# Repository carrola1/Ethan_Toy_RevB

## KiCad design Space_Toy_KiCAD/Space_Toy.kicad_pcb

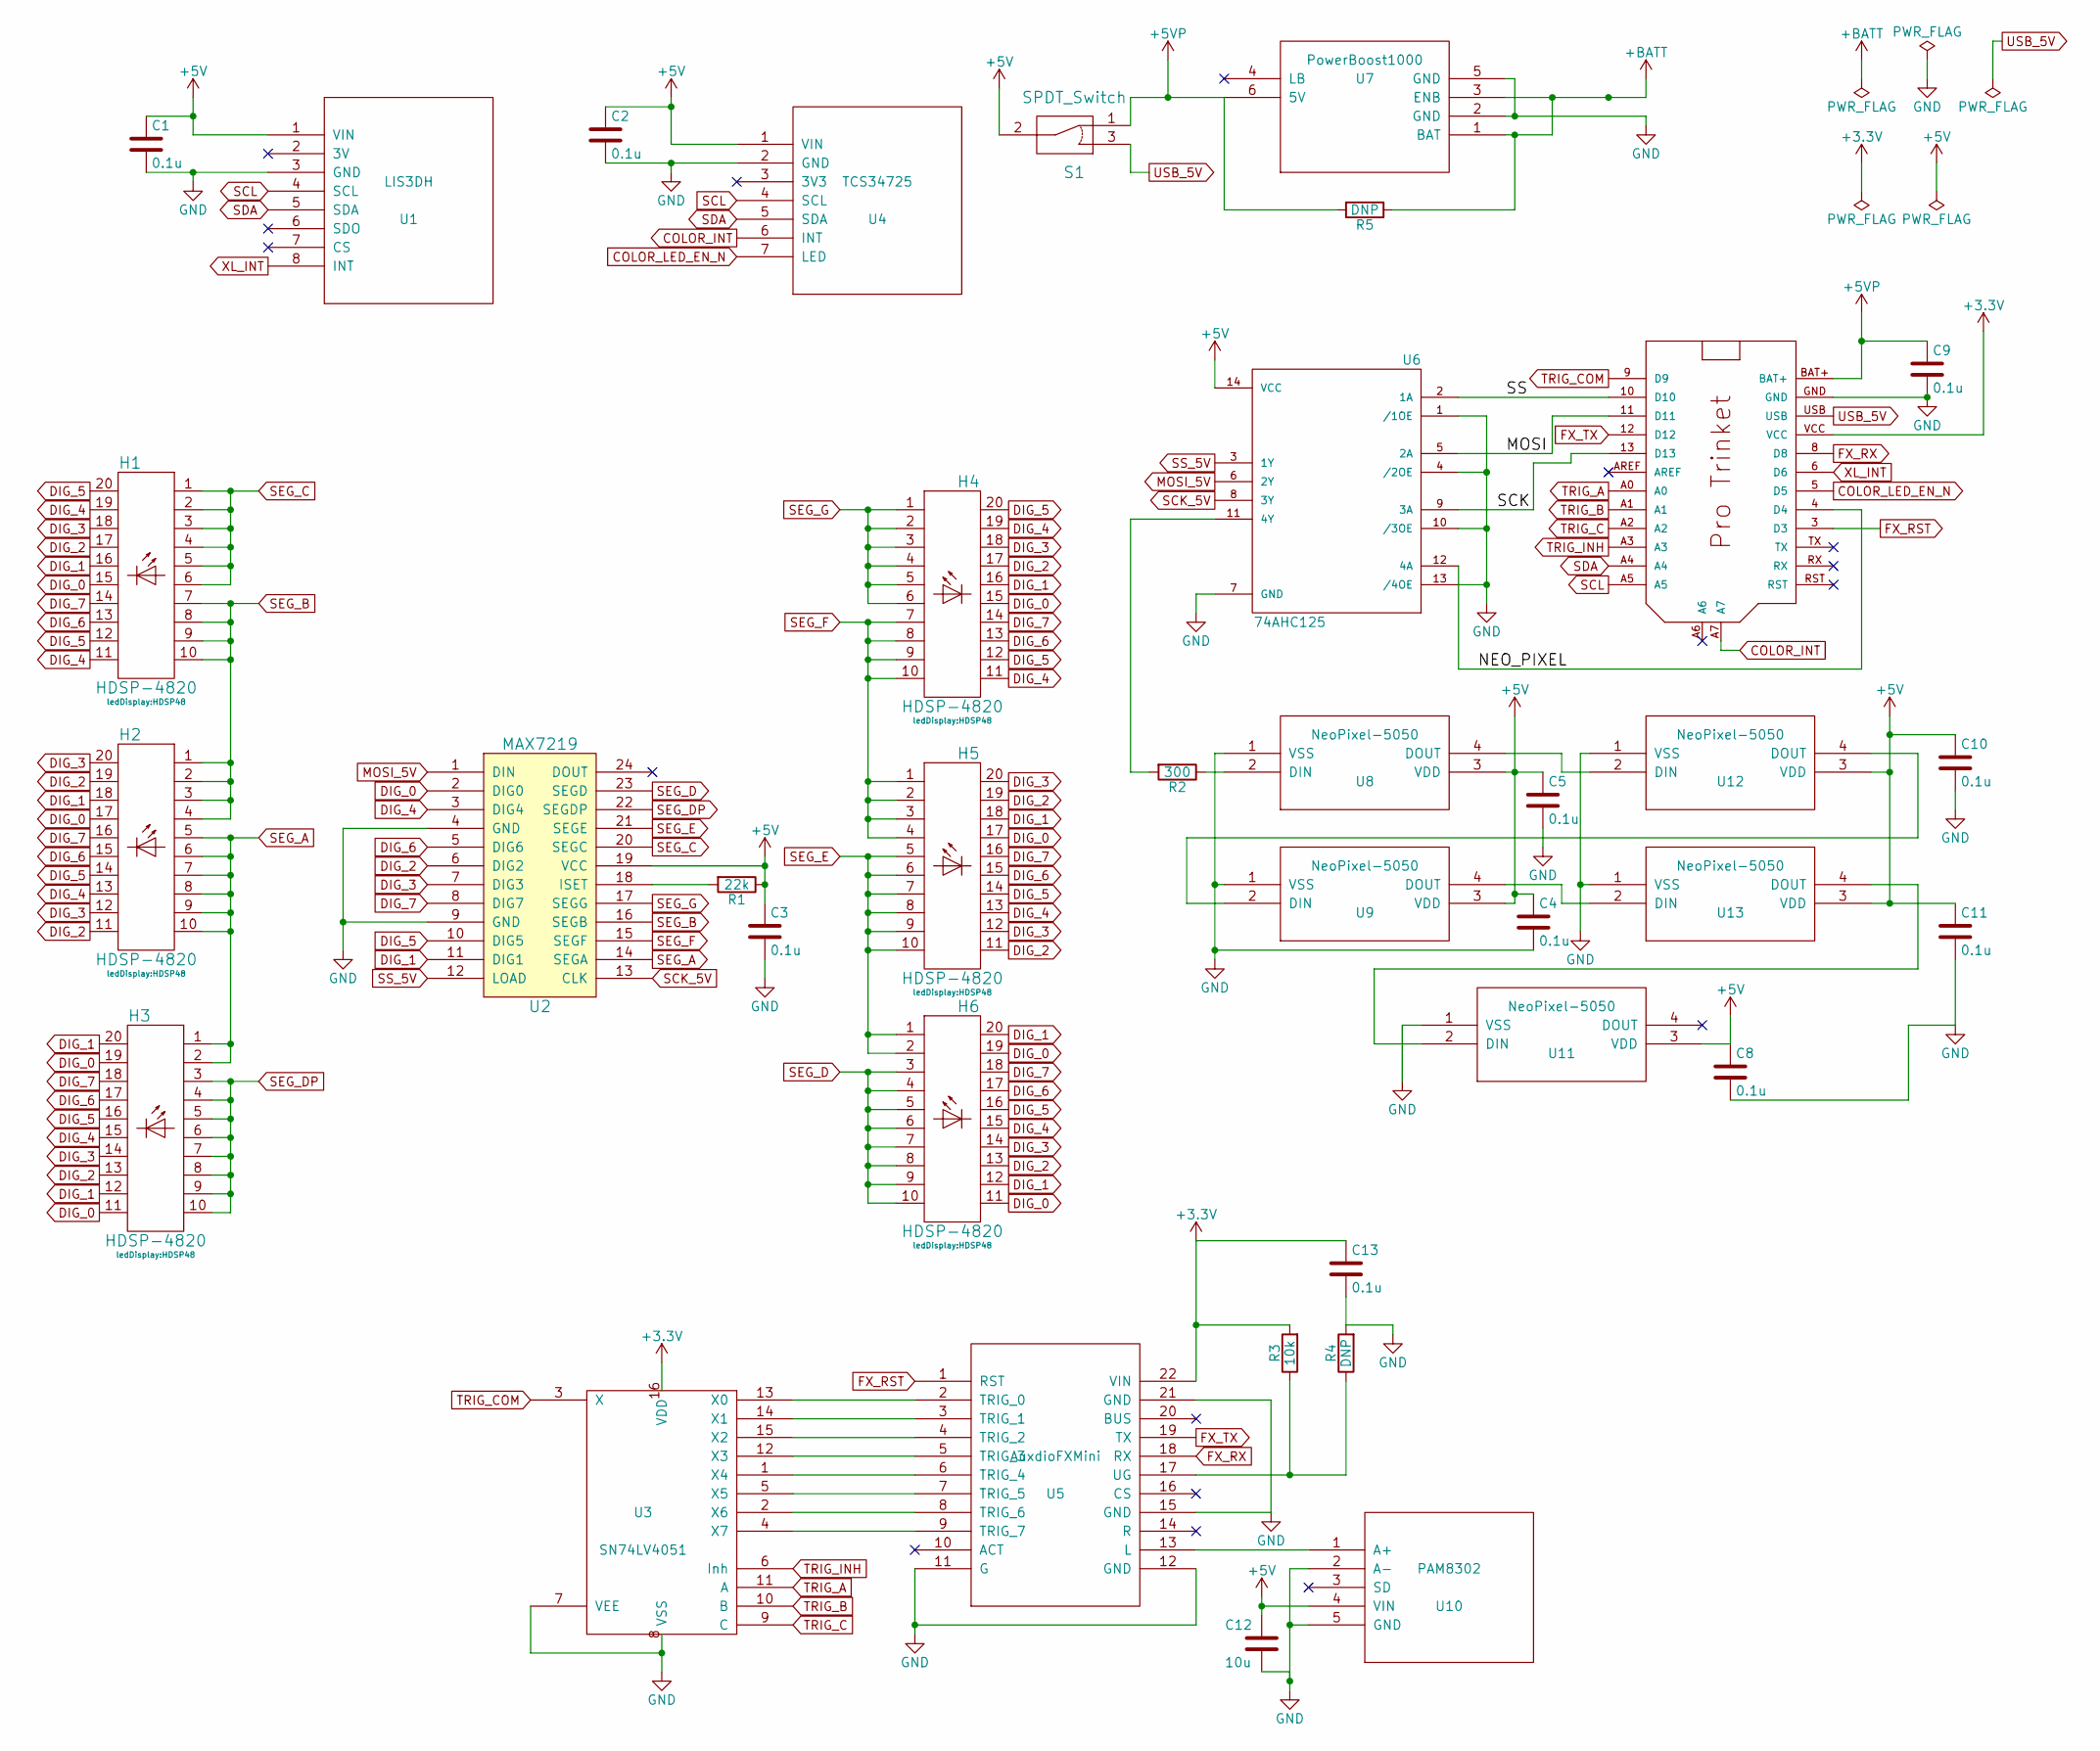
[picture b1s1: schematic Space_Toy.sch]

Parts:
C1, C2, C3, C4, C5, C8, C9, C10, C11, C13: 0.1u; C_0603_HandSoldering
C12: 10u; C_0603_HandSoldering
H1, H2, H3, H4, H5, H6: HDSP-4820; HDSP48
M1: PRO_TRINKET; PROTRINKET
R1: 22k; R_0805_HandSoldering
R2: 300; R_0805_HandSoldering
R3: 10k; R_0805_HandSoldering
R4, R5: DNP; R_0805_HandSoldering
S1: SPDT_Switch; SPDT
U1: LIS3DH
U2: MAX7219; DIP-24_W7.62mm_LongPads
U3: SN74LV4051; DIP-16_W7.62mm_LongPads
U4: TCS34725
U5: AuxdioFXMini; AudioFXMini
U6: 74AHC125; DIP-14_W7.62mm_LongPads
U7: PowerBoost1000
U8, U9, U11, U12, U13: NeoPixel-5050; NeoPixel5050
U10: PAM8302

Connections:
+3V3: C13.1, M1.VCC, R3.2, U3.16 (VDD), U5.22 (VIN)
+5V: C1.1, C2.1, C3.1, C4.1, C5.1, C8.1, C10.1, C11.1, C12.1, R1.1, S1.2, U1.1 (VIN), U2.19 (VCC), U4.1 (VIN), U6.14 (VCC), U8.3 (VDD), U9.3 (VDD), U10.4 (VIN), U11.3 (VDD), U12.3 (VDD), U13.3 (VDD)
+5VP: C9.1, M1.BAT+, R5.2, S1.1, U7.6 (5V)
+BATT: R5.1, U7.1 (BAT), U7.3 (ENB)
/MOSI: M1.11 (D11), U6.5 (2A)
/NEO_PIXEL: M1.4 (D4), U6.12 (4A)
/SCK: M1.13 (D13), U6.9 (3A)
/SS: M1.10 (D10), U6.2 (1A)
COLOR_INT: M1.A7, U4.6 (INT)
COLOR_LED_EN_N: M1.5 (D5), U4.7 (LED)
DIG_0: H1.15 (K), H2.17 (K), H3.11 (K), H3.19 (K), H4.15 (K), H5.17 (K), H6.11 (K), H6.19 (K), U2.2 (DIG0)
DIG_1: H1.16 (K), H2.18 (K), H3.12 (K), H3.20 (K), H4.16 (K), H5.18 (K), H6.12 (K), H6.20 (K), U2.11 (DIG1)
DIG_2: H1.17 (K), H2.11 (K), H2.19 (K), H3.13 (K), H4.17 (K), H5.11 (K), H5.19 (K), H6.13 (K), U2.6 (DIG2)
DIG_3: H1.18 (K), H2.12 (K), H2.20 (K), H3.14 (K), H4.18 (K), H5.12 (K), H5.20 (K), H6.14 (K), U2.7 (DIG3)
DIG_4: H1.11 (K), H1.19 (K), H2.13 (K), H3.15 (K), H4.11 (K), H4.19 (K), H5.13 (K), H6.15 (K), U2.3 (DIG4)
DIG_5: H1.12 (K), H1.20 (K), H2.14 (K), H3.16 (K), H4.12 (K), H4.20 (K), H5.14 (K), H6.16 (K), U2.10 (DIG5)
DIG_6: H1.13 (K), H2.15 (K), H3.17 (K), H4.13 (K), H5.15 (K), H6.17 (K), U2.5 (DIG6)
DIG_7: H1.14 (K), H2.16 (K), H3.18 (K), H4.14 (K), H5.16 (K), H6.18 (K), U2.8 (DIG7)
FX_RST: M1.3 (D3), U5.1 (RST)
FX_RX: M1.8 (D8), U5.18 (RX)
FX_TX: M1.12 (D12), U5.19 (TX)
GND: C1.2, C2.2, C3.2, C4.2, C5.2, C8.2, C9.2, C10.2, C11.2, C12.2, C13.2, M1.GND, R4.2, U1.3 (GND), U2.4 (GND), U2.9 (GND), U3.7 (VEE), U3.8 (VSS), U4.2 (GND), U5.11 (G), U5.12 (GND), U5.15 (GND), U5.21 (GND), U6.1 (/1OE), U6.4 (/2OE), U6.7 (GND), U6.10 (/3OE), U6.13 (/4OE), U7.2 (GND), U7.5 (GND), U8.1 (VSS), U9.1 (VSS), U10.2 (A-), U10.5 (GND), U11.1 (VSS), U12.1 (VSS), U13.1 (VSS)
MOSI_5V: U2.1 (DIN), U6.6 (2Y)
unnamed: R1.2, U2.18 (ISET)
unnamed: R2.1, U8.2 (DIN)
unnamed: R2.2, U6.11 (4Y)
unnamed: R3.1, R4.1, U5.17 (UG)
unnamed: U3.1 (X4), U5.6 (TRIG_4)
unnamed: U3.2 (X6), U5.8 (TRIG_6)
unnamed: U3.4 (X7), U5.9 (TRIG_7)
unnamed: U3.5 (X5), U5.7 (TRIG_5)
unnamed: U3.12 (X3), U5.5 (TRIG_3)
unnamed: U3.13 (X0), U5.2 (TRIG_0)
unnamed: U3.14 (X1), U5.3 (TRIG_1)
unnamed: U3.15 (X2), U5.4 (TRIG_2)
unnamed: U5.13 (L), U10.1 (A+)
unnamed: U11.2 (DIN), U13.4 (DOUT)
unnamed: U8.4 (DOUT), U12.2 (DIN)
unnamed: U9.2 (DIN), U12.4 (DOUT)
unnamed: U9.4 (DOUT), U13.2 (DIN)
SCK_5V: U2.13 (CLK), U6.8 (3Y)
SCL: M1.A5, U1.4 (SCL), U4.4 (SCL)
SDA: M1.A4, U1.5 (SDA), U4.5 (SDA)
SEG_A: H2.5 (A), H2.6 (A), H2.7 (A), H2.8 (A), H2.9 (A), H2.10 (A), H3.1 (A), H3.2 (A), U2.14 (SEGA)
SEG_B: H1.7 (A), H1.8 (A), H1.9 (A), H1.10 (A), H2.1 (A), H2.2 (A), H2.3 (A), H2.4 (A), U2.16 (SEGB)
SEG_C: H1.1 (A), H1.2 (A), H1.3 (A), H1.4 (A), H1.5 (A), H1.6 (A), U2.20 (SEGC)
SEG_D: H6.3 (A), H6.4 (A), H6.5 (A), H6.6 (A), H6.7 (A), H6.8 (A), H6.9 (A), H6.10 (A), U2.23 (SEGD)
SEG_DP: H3.3 (A), H3.4 (A), H3.5 (A), H3.6 (A), H3.7 (A), H3.8 (A), H3.9 (A), H3.10 (A), U2.22 (SEGDP)
SEG_E: H5.5 (A), H5.6 (A), H5.7 (A), H5.8 (A), H5.9 (A), H5.10 (A), H6.1 (A), H6.2 (A), U2.21 (SEGE)
SEG_F: H4.7 (A), H4.8 (A), H4.9 (A), H4.10 (A), H5.1 (A), H5.2 (A), H5.3 (A), H5.4 (A), U2.15 (SEGF)
SEG_G: H4.1 (A), H4.2 (A), H4.3 (A), H4.4 (A), H4.5 (A), H4.6 (A), U2.17 (SEGG)
SS_5V: U2.12 (LOAD), U6.3 (1Y)
TRIG_A: M1.A0, U3.11 (A)
TRIG_B: M1.A1, U3.10 (B)
TRIG_C: M1.A2, U3.9 (C)
TRIG_COM: M1.9 (D9), U3.3 (X)
TRIG_INH: M1.A3, U3.6 (Inh)
USB_5V: M1.USB, S1.3
XL_INT: M1.6 (D6), U1.8 (INT)

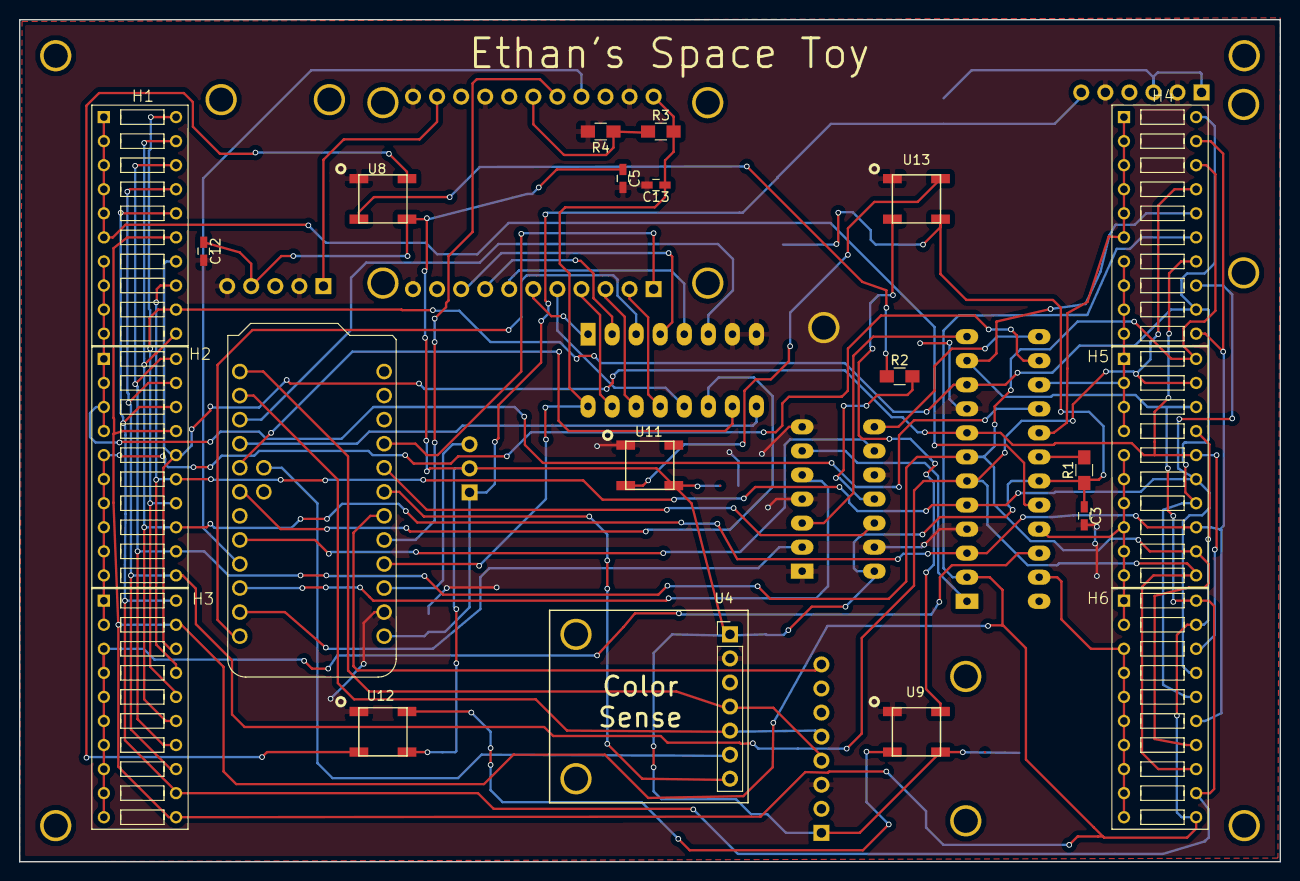
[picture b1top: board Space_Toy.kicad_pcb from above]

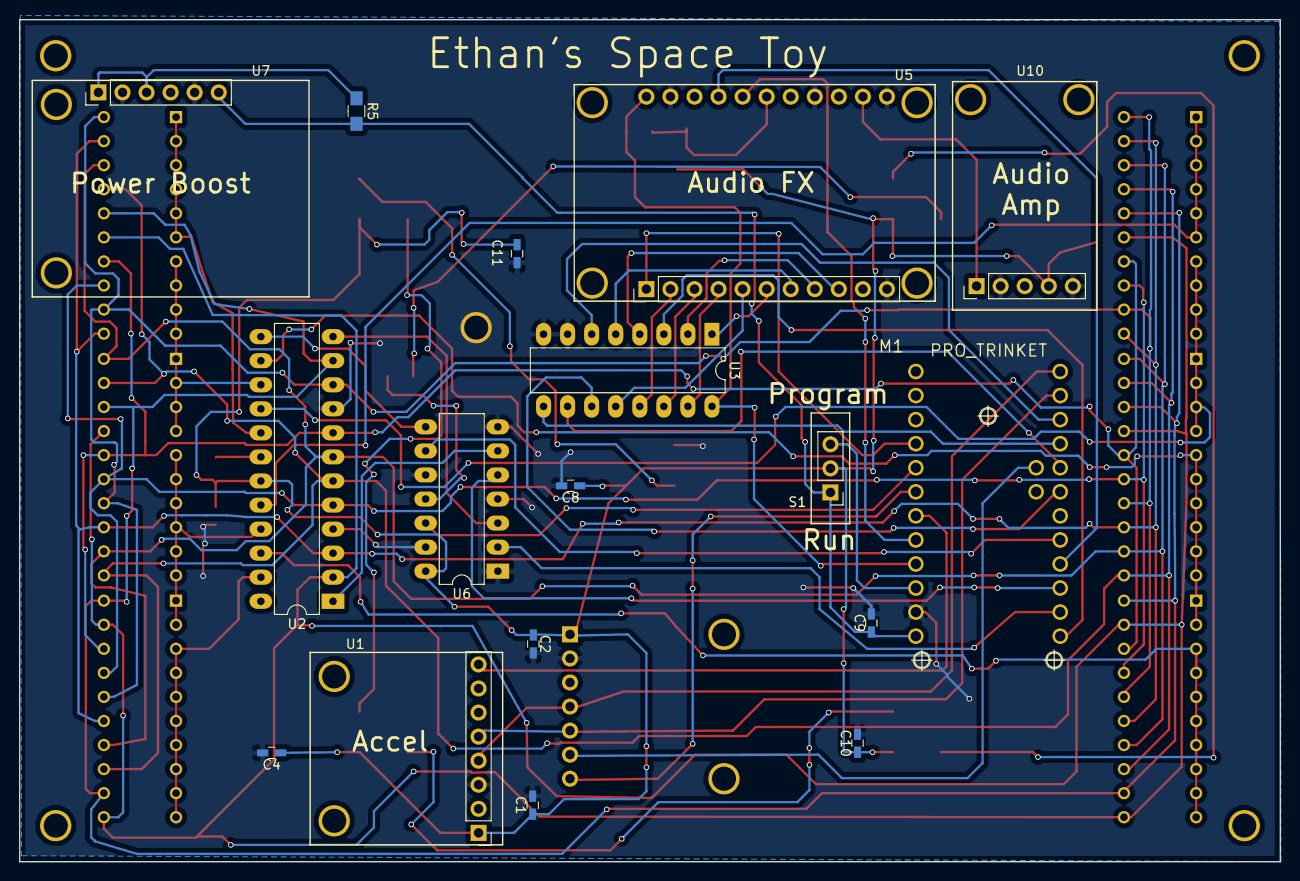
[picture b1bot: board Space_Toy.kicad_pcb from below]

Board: 2 copper layers, 133.1 x 88.9 mm, 37 parts (17 on the bottom side), 59 nets.

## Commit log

2017-08-15 First try
2017-08-20 Added audio, accelerometer, LED support
2017-09-21 Fully functional
2017-09-24 Added rocket animation
